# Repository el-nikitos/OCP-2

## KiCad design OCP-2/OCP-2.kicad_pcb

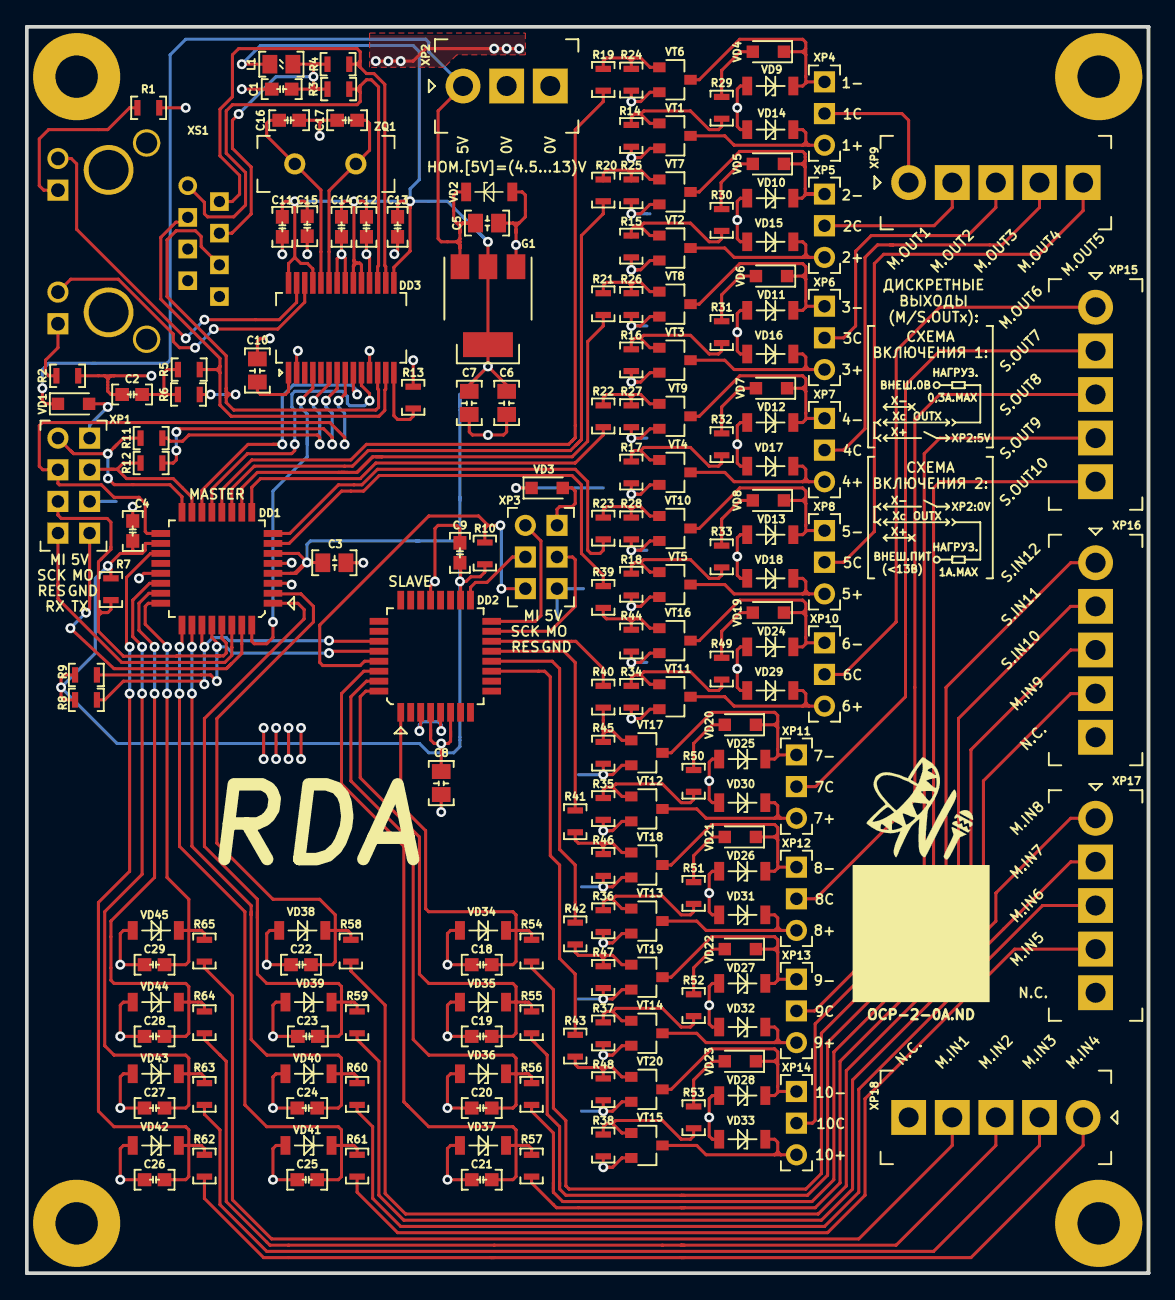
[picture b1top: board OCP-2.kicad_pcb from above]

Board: 2 copper layers, 90.0 x 100.0 mm, 189 parts (0 on the bottom side), 130 nets.

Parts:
C1, C2, C4, C9, C11, C12, C13, C14, C15, C18, C19, C20, C21, C22, C23, C24, C25, C26, C27, C28, C29: Конденсатор*0,1мкФ*25В*0603; Конденсатор_SMD_IEC_0603
C3, C5, C6, C7, C8, C10: Конденсатор*10мкФ*16В*0805; Конденсатор_SMD_IEC_0805
C16, C17: Конденсатор*12пФ*50В*0603; Конденсатор_SMD_IEC_0603
DD1: МК*ATmega168*TQFP32; микросхема_ATMEGA-8-161AU
DD2: МК*ATmega88*TQFP32; микросхема_ATMEGA-8-161AU
DD3: Преобразователь*ETH-SPI*SSOP28; SSOP-28
G1: LDO*вход_18Вmax*выход_3,3В*ток_1,2АSOT-223; Транзистор_NPN_SOT223_pnp
L1: Чип-индуктивность*0,56мкГн*150мА*0805; Резистор_SMD_IEC_0805_0,125_Вт
R1, R2, R11, R12, R19, R20, R21, R22, R23, R29, R30, R31, R32, R33, R39, R40, R41, R42, R43, R49, R50, R51, R52, R53, R54, R55, R56, R57, R58, R59, R60, R61, R62, R63, R64, R65: Резистор*1кОм*0603; Резистор_SMD_0603_0,065_Вт_pnp
R3, R4, R5, R6: Резистор*49,9кОм*0603; Резистор_SMD_0603_0,065_Вт_pnp
R7, R8, R9, R10, R14, R15, R16, R17, R18, R24, R25, R26, R27, R28, R34, R35, R36, R37, R38, R44, R45, R46, R47, R48: Резистор*10кОм*0603; Резистор_SMD_0603_0,065_Вт_pnp
R13: Резистор*2,32кОм*0603; Резистор_SMD_0603_0,065_Вт_pnp
VD1, VD3, VD4, VD5, VD6, VD7, VD8, VD19, VD20, VD21, VD22, VD23: Диод*75В*0,2А*SOD-323; D_SOD-323_HandSoldering
VD2, VD9, VD10, VD11, VD12, VD13, VD14, VD15, VD16, VD17, VD18, VD24, VD25, VD26, VD27, VD28, VD29, VD30, VD31, VD32, VD33: Стабилитрон*7,5В*SOD80; SOD-80
VD34, VD35, VD36, VD37, VD38, VD39, VD40, VD41, VD42, VD43, VD44, VD45: Стабилитрон*3,9В*SOD80; SOD-80
VT1, VT2, VT3, VT4, VT5, VT11, VT12, VT13, VT14, VT15: Транзистор*pnp*0,5А*45В*SOT23; Корпус_КТ-46
VT6, VT7, VT8, VT9, VT10, VT16, VT17, VT18, VT19, VT20: Транзистор*npn*0,5А*45В*SOT23; Корпус_КТ-46
X1, X2, X3, X4: ico*отверстие*М3; Отверстие_М3
X5: ico*LOGO_NIKITOS_10х10; ni_10x10
XP1: Вилка*PLD*8контактов*2ряда*вертикальная*AVR+UART; Вилка_PLD8_вертикальная_AB
XP2: Клеммник*шаг_3,5*3контактов*1ряд*вертикальная; Клеммник_15EDGVC-3.5-03P
XP3: Вилка*PLD*6контактов*2ряда*вертикальная*AVR; Вилка_PLD6_вертикальная_AB
XP4, XP5, XP6, XP7, XP8, XP10, XP11, XP12, XP13, XP14: Вилка*PLS*3контактов*1ряд*вертикальная; Вилка_PLS3_вертикальная
XP9, XP15, XP16, XP17, XP18: Клеммник*шаг_3,5*5контактов*1ряд*вертикальная; Клеммник_15EDGVC-3.5-05P
XS1: Розетка*ETH+трансформатор*8p8c; Розетка_ETH_KLS12-TL002
ZQ1: Резонатор*25МГц*HC-49U; Резонатор_РК456МДУ(DIP)

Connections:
3V3: C3.1, C4.1, C6.1, C7.1, C8.1, C9.1, C11.1, C12.1, C13.1, C14.1, C15.1, DD1.4, DD1.6, DD1.18, DD2.4, DD2.6, DD2.18, DD3.15, DD3.19, DD3.20, DD3.25, DD3.28, G1.2, G1.4, L1.1, R7.1, R8.1, R9.1, R10.1
4...15V: C5.1, G1.3, R14.1, R15.1, R16.1, R17.1, R18.1, R34.1, R35.1, R36.1, R37.1, R38.1, VD1.1, VD2.2, VD3.1, VT1.2, VT2.2, VT3.2, VT4.2, VT5.2, VT11.2, VT12.2, VT13.2, VT14.2, VT15.2, XP2.1
/5V.M: VD1.2, XP1.1B
/5V.S: VD3.2, XP3.1B
/DIN1: R65.2, XP18.4
/DIN2: R64.2, XP18.3
/DIN3: R63.2, XP18.2
/DIN4: R62.2, XP18.1
/DIN5: R61.2, XP17.4
/DIN6: R60.2, XP17.3
/DIN7: R59.2, XP17.2
/DIN8: R58.2, XP17.1
/DIN9: R57.2, XP16.4
/DIN10: R56.2, XP16.3
/DIN11: R55.2, XP16.2
/DIN12: R54.2, XP16.1
/DOUT1: XP4.2, XP9.1
/DOUT1.NPN: VD4.1, VD9.2, VT6.3, XP4.3
/DOUT1.PNP: VD14.2, VT1.3, XP4.1
/DOUT2: XP5.2, XP9.2
/DOUT2.NPN: VD5.1, VD10.2, VT7.3, XP5.3
/DOUT2.PNP: VD15.2, VT2.3, XP5.1
/DOUT3: XP6.2, XP9.3
/DOUT3.NPN: VD6.1, VD11.2, VT8.3, XP6.3
/DOUT3.PNP: VD16.2, VT3.3, XP6.1
/DOUT4: XP7.2, XP9.4
/DOUT4.NPN: VD7.1, VD12.2, VT9.3, XP7.3
/DOUT4.PNP: VD17.2, VT4.3, XP7.1
/DOUT5: XP8.2, XP9.5
/DOUT5.NPN: VD8.1, VD13.2, VT10.3, XP8.3
/DOUT5.PNP: VD18.2, VT5.3, XP8.1
/DOUT6: XP10.2, XP15.1
/DOUT6.NPN: VD19.1, VD24.2, VT16.3, XP10.3
/DOUT6.PNP: VD29.2, VT11.3, XP10.1
/DOUT7: XP11.2, XP15.2
/DOUT7.NPN: VD20.1, VD25.2, VT17.3, XP11.3
/DOUT7.PNP: VD30.2, VT12.3, XP11.1
/DOUT8: XP12.2, XP15.3
/DOUT8.NPN: VD21.1, VD26.2, VT18.3, XP12.3
/DOUT8.PNP: VD31.2, VT13.3, XP12.1
/DOUT9: XP13.2, XP15.4
/DOUT9.NPN: VD22.1, VD27.2, VT19.3, XP13.3
/DOUT9.PNP: VD32.2, VT14.3, XP13.1
/DOUT10: XP14.2, XP15.5
/DOUT10.NPN: VD23.1, VD28.2, VT20.3, XP14.3
/DOUT10.PNP: VD33.2, VT15.3, XP14.1
/ETH.CLK: DD1.17, DD3.8, XP1.2A
/ETH.CS: DD1.14, DD3.9
/ETH.INT: DD1.32, DD3.4
/ETH.MISO: DD1.16, R11.2, XP1.1A
/ETH.MOSI: DD1.15, R12.2, XP1.2B
/ETH.RES: DD1.13, DD3.10
/EXR.CAP: C10.2, DD3.1
/LEDA: DD3.27, XS1.9
/LEDB: DD3.26, XS1.11
/MC.DIN1: C29.2, DD1.24, R65.1, VD45.2
/MC.DIN2: C28.2, DD1.23, R64.1, VD44.2
/MC.DIN3: C27.2, DD1.22, R63.1, VD43.2
/MC.DIN4: C26.2, DD1.19, R62.1, VD42.2
/MC.DIN5: C25.2, DD1.25, R61.1, VD41.2
/MC.DIN6: C24.2, DD1.26, R60.1, VD40.2
/MC.DIN7: C23.2, DD1.1, R59.1, VD39.2
/MC.DIN8: C22.2, DD1.2, R58.1, VD38.2
/MC.DIN9: C21.2, DD2.30, R57.1, VD37.2
/MC.DIN10: C20.2, DD2.31, R56.1, VD36.2
/MC.DIN11: C19.2, DD2.32, R55.1, VD35.2
/MC.DIN12: C18.2, DD2.1, R54.1, VD34.2
/MC.OUT1: DD1.12, R19.1
/MC.OUT2: DD1.11, R20.1
/MC.OUT3: DD1.10, R21.1
/MC.OUT4: DD1.9, R22.1
/MC.OUT5: DD1.8, R23.1
/MC.OUT6: DD1.7, R39.1
/MC.OUT7: DD2.14, R40.1
/MC.OUT8: DD2.13, R41.1
/MC.OUT9: DD2.12, R42.1
/MC.OUT10: DD2.11, R43.1
/MID-TX: C1.1, L1.2, R3.1, R4.2, XS1.4
/MISO.S: DD2.16, XP3.1A
/MOSI.S: DD2.15, XP3.2B
/OSC1: C17.1, DD3.23, ZQ1.2
/OSC2: C16.1, DD3.24, ZQ1.1
/RBIAS: DD3.14, R13.1
/RES.M: DD1.29, R7.2, XP1.3A
/RES.S: DD2.29, R10.2, XP3.3A
/RX: DD1.30, XP1.4A
/SCK.S: DD2.17, XP3.2A
/SCL: DD1.28, DD2.28, R9.2
/SDA: DD1.27, DD2.27, R8.2
/TPIN+: DD3.13, R5.2, XS1.3
/TPIN-: DD3.12, R6.1, XS1.6
/TPOUT+: DD3.17, R3.2, XS1.1
/TPOUT-: DD3.16, R4.1, XS1.2
/TX: DD1.31, XP1.4B
GND: C1.2, C2.2, C3.2, C4.2, C5.2, C6.2, C7.2, C8.2, C9.2, C10.1, C11.2, C12.2, C13.2, C14.2, C15.2, C16.2, C17.2, C18.1, C19.1, C20.1, C21.1, C22.1, C23.1, C24.1, C25.1, C26.1, C27.1, C28.1, C29.1, DD1.3, DD1.5, DD1.21, DD2.3, DD2.5, DD2.21, DD3.2, DD3.11, DD3.18, DD3.21, DD3.22, G1.1, R1.2, R2.2, R13.2, R24.2, R25.2, R26.2, R27.2, R28.2, R44.2, R45.2, R46.2, R47.2, R48.2, VD2.1, VD9.1, VD10.1, VD11.1, VD12.1, VD13.1, VD14.1, VD15.1, VD16.1, VD17.1, VD18.1, VD24.1, VD25.1, VD26.1, VD27.1, VD28.1, VD29.1, VD30.1, VD31.1, VD32.1, VD33.1, VD34.1, VD35.1, VD36.1, VD37.1, VD38.1, VD39.1, VD40.1, VD41.1, VD42.1, VD43.1, VD44.1, VD45.1, VT6.2, VT7.2, VT8.2, VT9.2, VT10.2, VT16.2, VT17.2, VT18.2, VT19.2, VT20.2, XP1.3B, XP2.2, XP2.3, XP3.3B, XS1.8
unnamed: C2.1, R5.1, R6.2
unnamed: DD3.6, R11.1
unnamed: DD3.7, R12.1
unnamed: R1.1, XS1.10
unnamed: R2.1, XS1.12
unnamed: R14.2, R29.2, VT1.1
unnamed: R15.2, R30.2, VT2.1
unnamed: R16.2, R31.2, VT3.1
unnamed: R17.2, R32.2, VT4.1
unnamed: R18.2, R33.2, VT5.1
unnamed: R19.2, R24.1, VT6.1
unnamed: R20.2, R25.1, VT7.1
unnamed: R21.2, R26.1, VT8.1
unnamed: R22.2, R27.1, VT9.1
unnamed: R23.2, R28.1, VT10.1
unnamed: R29.1, VD4.2
unnamed: R30.1, VD5.2
unnamed: R31.1, VD6.2
unnamed: R32.1, VD7.2
unnamed: R33.1, VD8.2
unnamed: R34.2, R49.2, VT11.1
unnamed: R35.2, R50.2, VT12.1
unnamed: R36.2, R51.2, VT13.1
unnamed: R37.2, R52.2, VT14.1
unnamed: R38.2, R53.2, VT15.1
unnamed: R39.2, R44.1, VT16.1
unnamed: R40.2, R45.1, VT17.1
unnamed: R41.2, R46.1, VT18.1
unnamed: R42.2, R47.1, VT19.1
unnamed: R43.2, R48.1, VT20.1
unnamed: R49.1, VD19.2
unnamed: R50.1, VD20.2
unnamed: R51.1, VD21.2
unnamed: R52.1, VD22.2
unnamed: R53.1, VD23.2

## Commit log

2021-11-14 2 МК + ETH-SPI
2021-11-14 обвес питания МК и ETH
2021-11-20 схема DI и DO + трассировка
2021-11-21 размещена угловая розетка модуля
2021-11-21 размещена схема DI, схема не подбита
2021-12-01 изменена вилка программирования, вынесена розетка ETH
2021-12-02 схема подключения ETH без SPI и светодиодов
2021-12-03 полная схема подключен ETH и МК, нет клеммников
2021-12-05 схема включения ETH + клеммники вместо СНП306
2021-12-09 перенесены клеммники, +LDO, +прог.разъем, +МК расположение
2021-12-11 завершенеа трассировка
2021-12-11 добавлена поясняющая маркировка
2021-12-11 добавлены запирающие диоды в npn канал, обновлен step
2021-12-12 0А: добавлены диодная защита прог. + стабилитрон на входе питания
2021-12-12 OCP-2-0A-CU_only: добавлена пустая заливка обратной стороны
2021-12-19 ссылки в элементах исправлены под заказ
2021-12-23 перечень ПКИ для КД
2021-12-28 управление DO1-4 через http
2021-12-29 определена кастомные функции работы с gpio
2021-12-30 все GPIO через кастомные функции +6 канал +логика перенесена в регистр
2021-12-30 добавлена рыба для дискретных входов, исправлена ошибка с битым символом
2022-01-01 настроены DI и DO для мастера + web-лицо
2022-01-01 добавлен вывод в HTML регистров
2022-01-06 i2c-slave din & dout + eth i2c-master
2022-01-07 начата описательная часть
2022-02-20 файлы для подключения кастомных плат
2022-02-27 обновлена документация, добавлена резервная копия avrdude
